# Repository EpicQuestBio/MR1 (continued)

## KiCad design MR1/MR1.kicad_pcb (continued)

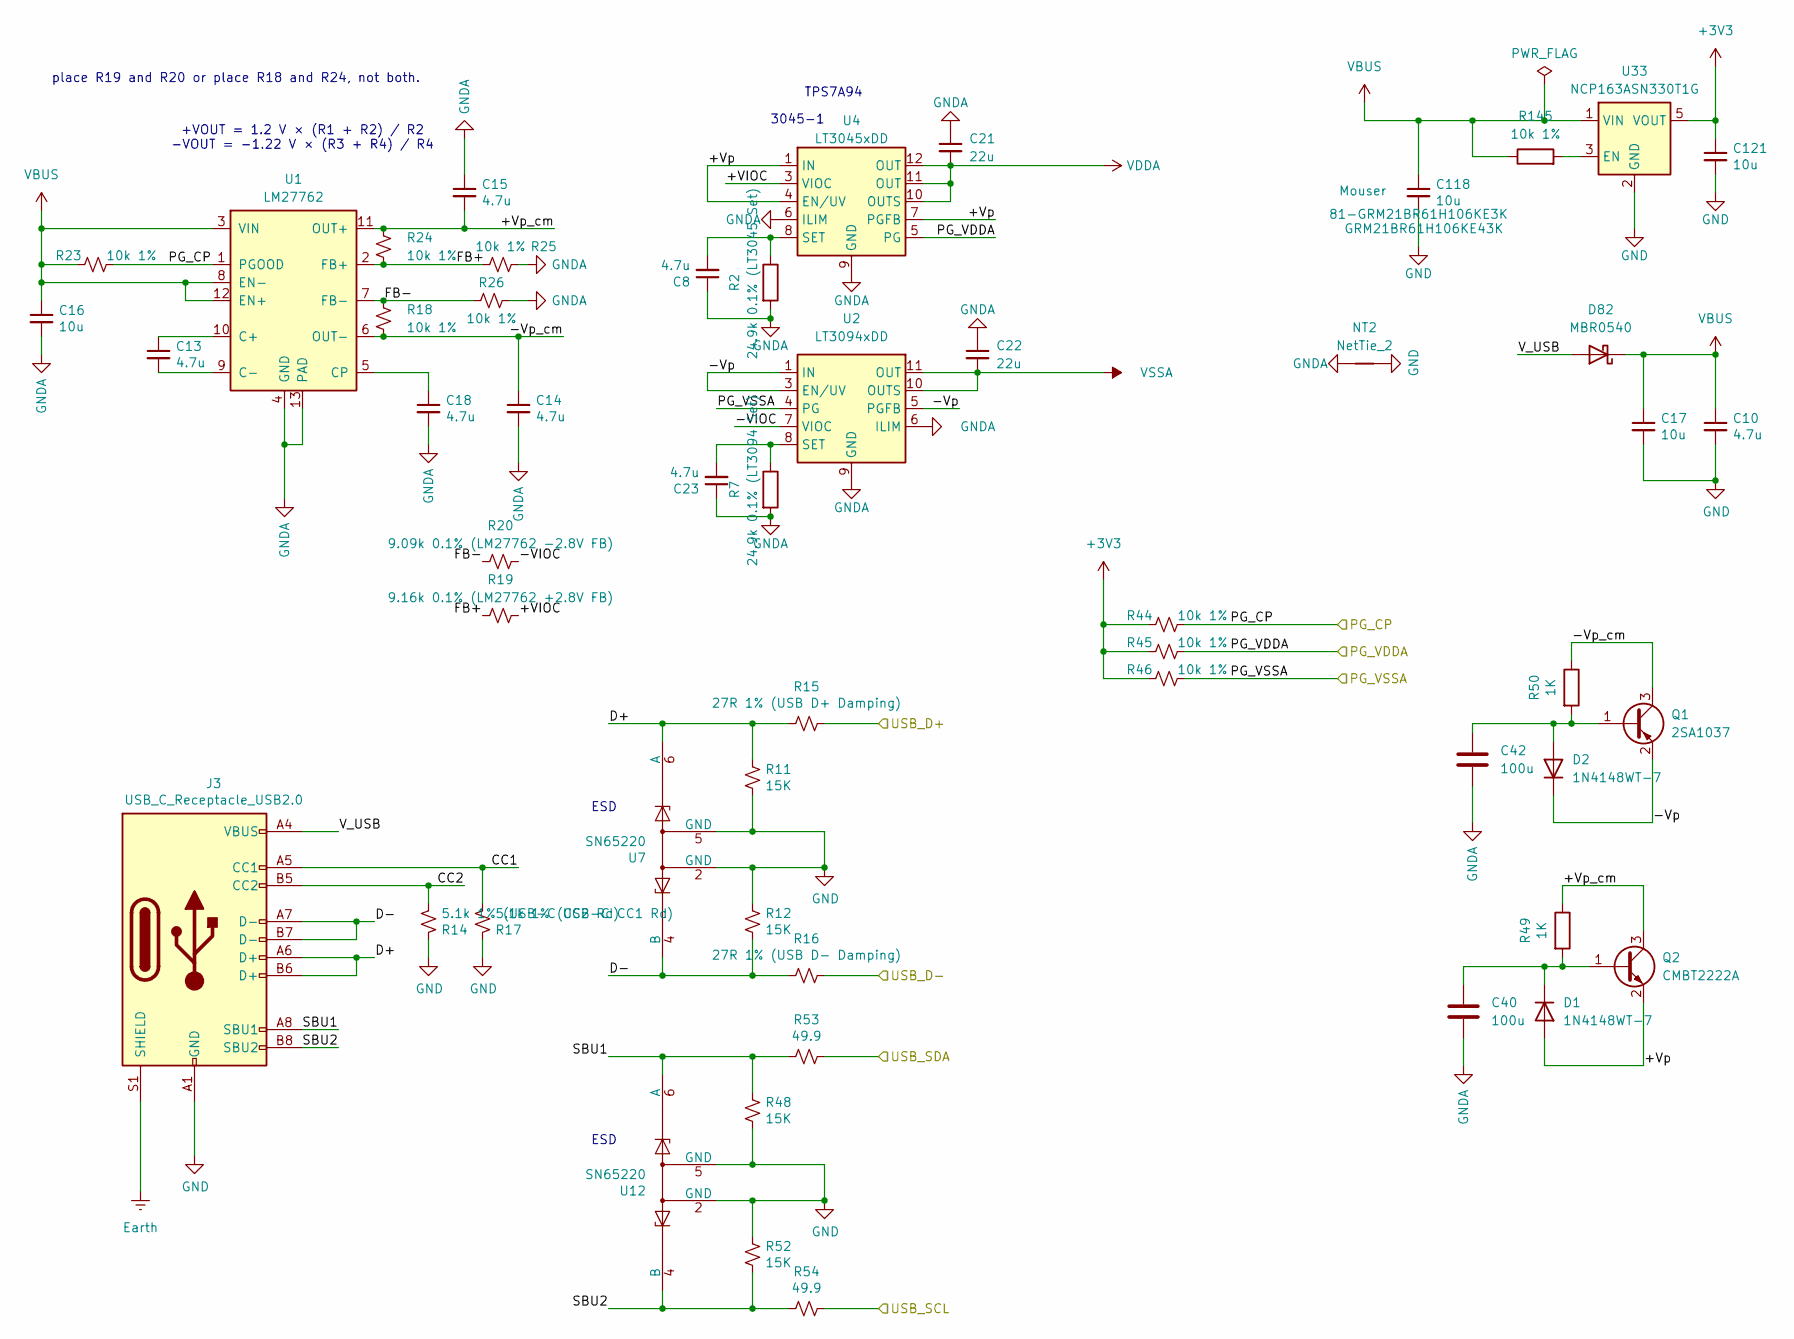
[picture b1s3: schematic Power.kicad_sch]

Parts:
C8, C10, C13, C14, C15, C18, C23: 4.7u; C_0402_1005Metric; Manufacturer_Part_Number JMK107C6475KA-T; LCSC C23733
C16, C17: 10u; C_0402_1005Metric; Manufacturer_Part_Number LMK212ABJ106MG-T; LCSC C15525
C21, C22: 22u; C_0402_1005Metric; MPN GRM21BR61H106KE43K; LCSC C2762589
C40, C42: 100u; C_1206_3216Metric; LCSC C15008
C118, C121: 10u; C_0402_1005Metric; MPN GRM21BR61H106KE43K; LCSC C15525
D1, D2: 1N4148WT-7; D_SOD-523; LCSC C727112
D82: MBR0540; D_SOD-123; MPN MBR0540L-TP; LCSC C5204747
J3: USB_C_Receptacle_USB2.0; USB_C_Receptacle_HRO_TYPE-C-31-M-12; Manufacturer_Part_Number USB4105-GF-A; LCSC C165948
NT2: NetTie_2; NetTie-2_SMD_Pad0.5mm
Q1: 2SA1037; SOT-23; LCSC C2143
Q2: CMBT2222A; SOT-23; LCSC C2152
R2: 24.9k 0.1% (LT3045 Set); R_0402_1005Metric; LCSC C25874
R7: 24.9k 0.1% (LT3094 Set); R_0402_1005Metric; LCSC C25874
R11, R12, R48, R52: 15K; R_0402_1005Metric; Manufacturer_Part_Number RC0603FR-1315KL; LCSC C25756
R14: 5.1k 1% (USB-C CC2 Rd); R_0402_1005Metric; Manufacturer_Part_Number CR0603-FX-5101ELF; LCSC C25905
R15: 27R 1% (USB D+ Damping); R_0402_1005Metric; Manufacturer_Part_Number RK73B1JTTDD270J; LCSC C25078
R16: 27R 1% (USB D- Damping); R_0402_1005Metric; Manufacturer_Part_Number RK73B1JTTDD270J; LCSC C25078
R17: 5.1k 1% (USB-C CC1 Rd); R_0402_1005Metric; Manufacturer_Part_Number CR0603-FX-5101ELF; LCSC C25905
R18, R23, R24, R25, R26, R44, R45, R46, R145: 10k 1%; R_0402_1005Metric; MPN RK73H1ETTPB1002F; LCSC C60490
R19: 9.16k 0.1% (LM27762 +2.8V FB); R_0402_1005Metric; MPN RK73H1ETTPB1002F; LCSC C11549
R20: 9.09k 0.1% (LM27762 -2.8V FB); R_0402_1005Metric; MPN RK73H1ETTPB1002F; LCSC C25879
R49, R50: 1K; R_0402_1005Metric; LCSC C11702
R53, R54: 49.9; R_0402_1005Metric; Manufacturer_Part_Number RK73B1JTTDD270J; LCSC C87044
U1: LM27762; WSON-12-1EP_3x2mm_P0.5mm_EP1x2.65_ThermalVias; MPN LM27762DSSR; LCSC C473398
U2: LT3094xDD; DFN-12-1EP_3x3mm_P0.45mm_EP1.65x2.38mm_ThermalVias; LCSC C670493
U4: LT3045xDD; DFN-12-1EP_3x3mm_P0.5mm_EP1.6x2.5mm; MPN LT3045EDD-1#TRPBF; LCSC C514420
U7, U12: SN65220; SOT-23-6; Manufacturer_Part_Number SN65220DBVT; LCSC C21787
U33: NCP163ASN330T1G; SOT-23-5; MPN NCP163ASN330T1G; LCSC C136082

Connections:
+3V3: C121.1, R44.1, R45.1, R46.1, U33.5 (VOUT); also elsewhere on the board
/Microcontroller/GPIO19: R16.2; also elsewhere on the board
/Microcontroller/GPIO20: R15.2; also elsewhere on the board
/Microcontroller/GPIO21: R53.2; also elsewhere on the board
/Microcontroller/GPIO26: R54.2; also elsewhere on the board
/Power/+VIOC: R19.1, U4.3 (VIOC)
/Power/+Vp: D1.2 (A), Q2.2 (E), U4.1 (IN), U4.2 (IN), U4.4 (EN/UV), U4.7 (PGFB)
/Power/+Vp_cm: C15.2, Q2.3 (C), R24.2, R49.1, U1.11 (OUT+)
/Power/-VIOC: R20.1, U2.7 (VIOC)
/Power/-Vp: D2.1 (K), Q1.2 (E), U2.1 (IN), U2.2 (IN), U2.3 (EN/UV), U2.5 (PGFB), U2.13 (IN)
/Power/-Vp_cm: C14.1, Q1.3 (C), R18.1, R50.1, U1.6 (OUT-)
/Power/CC1: J3.A5 (CC1), R17.2
/Power/CC2: J3.B5 (CC2), R14.2
/Power/D+: J3.A6 (D+), J3.B6 (D+), R11.1, R15.1, U7.1, U7.6 (A)
/Power/D-: J3.A7 (D-), J3.B7 (D-), R12.2, R16.1, U7.3, U7.4 (B)
/Power/FB+: R19.2, R24.1, R25.2, U1.2 (FB+)
/Power/FB-: R18.2, R20.2, R26.1, U1.7 (FB-)
/Power/PG_CP: R23.2, R44.2, U1.1 (PGOOD); also elsewhere on the board
/Power/PG_VDDA: R45.2, U4.5 (PG); also elsewhere on the board
/Power/PG_VSSA: R46.2, U2.4 (PG); also elsewhere on the board
/Power/SBU1: J3.A8 (SBU1), R48.1, R53.1, U12.1, U12.6 (A)
/Power/SBU2: J3.B8 (SBU2), R52.2, R54.1, U12.3, U12.4 (B)
/Power/V_USB: D82.2 (A), J3.A4 (VBUS), J3.A9 (VBUS), J3.B4 (VBUS), J3.B9 (VBUS)
Earth: J3.S1 (SHIELD); also elsewhere on the board
GND: C10.2, C17.2, C118.2, C121.2, J3.A1 (GND), J3.A12 (GND), J3.B1 (GND), J3.B12 (GND), NT2.2, R11.2, R12.1, R14.1, R17.1, R48.2, R52.1, U7.2 (GND), U7.5 (GND), U12.2 (GND), U12.5 (GND), U33.2 (GND); also elsewhere on the board
GNDA: C8.1, C14.2, C15.1, C16.2, C18.2, C21.1, C22.1, C23.1, C40.2, C42.1, NT2.1, R2.2, R7.2, R25.1, R26.2, U1.4 (GND), U1.13 (PAD), U2.6 (ILIM), U2.9 (GND), U4.6 (ILIM), U4.9 (GND), U4.13 (GND); also elsewhere on the board
unnamed: C40.1, D1.1 (K), Q2.1 (B), R49.2
unnamed: C42.2, D2.2 (A), Q1.1 (B), R50.2
unnamed: C13.1, U1.10 (C+)
unnamed: C13.2, U1.9 (C-)
unnamed: C18.1, U1.5 (CP)
unnamed: C23.2, R7.1, U2.8 (SET)
unnamed: C8.2, R2.1, U4.8 (SET)
unnamed: R145.2, U33.3 (EN)
VBUS: C10.1, C16.1, C17.1, C118.1, D82.1 (K), R23.1, R145.1, U1.3 (VIN), U1.8 (EN-), U1.12 (EN+), U33.1 (VIN)
VDDA: C21.2, U4.10 (OUTS), U4.11 (OUT), U4.12 (OUT); also elsewhere on the board
VSSA: C22.2, U2.10 (OUTS), U2.11 (OUT), U2.12 (OUT); also elsewhere on the board

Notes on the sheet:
ESD
+VOUT = 1.2 V × (R1 + R2) / R2 -VOUT = -1.22 V × (R3 + R4) / R4
3045-1
TPS7A94
place R19 and R20 or place R18 and R24, not both.

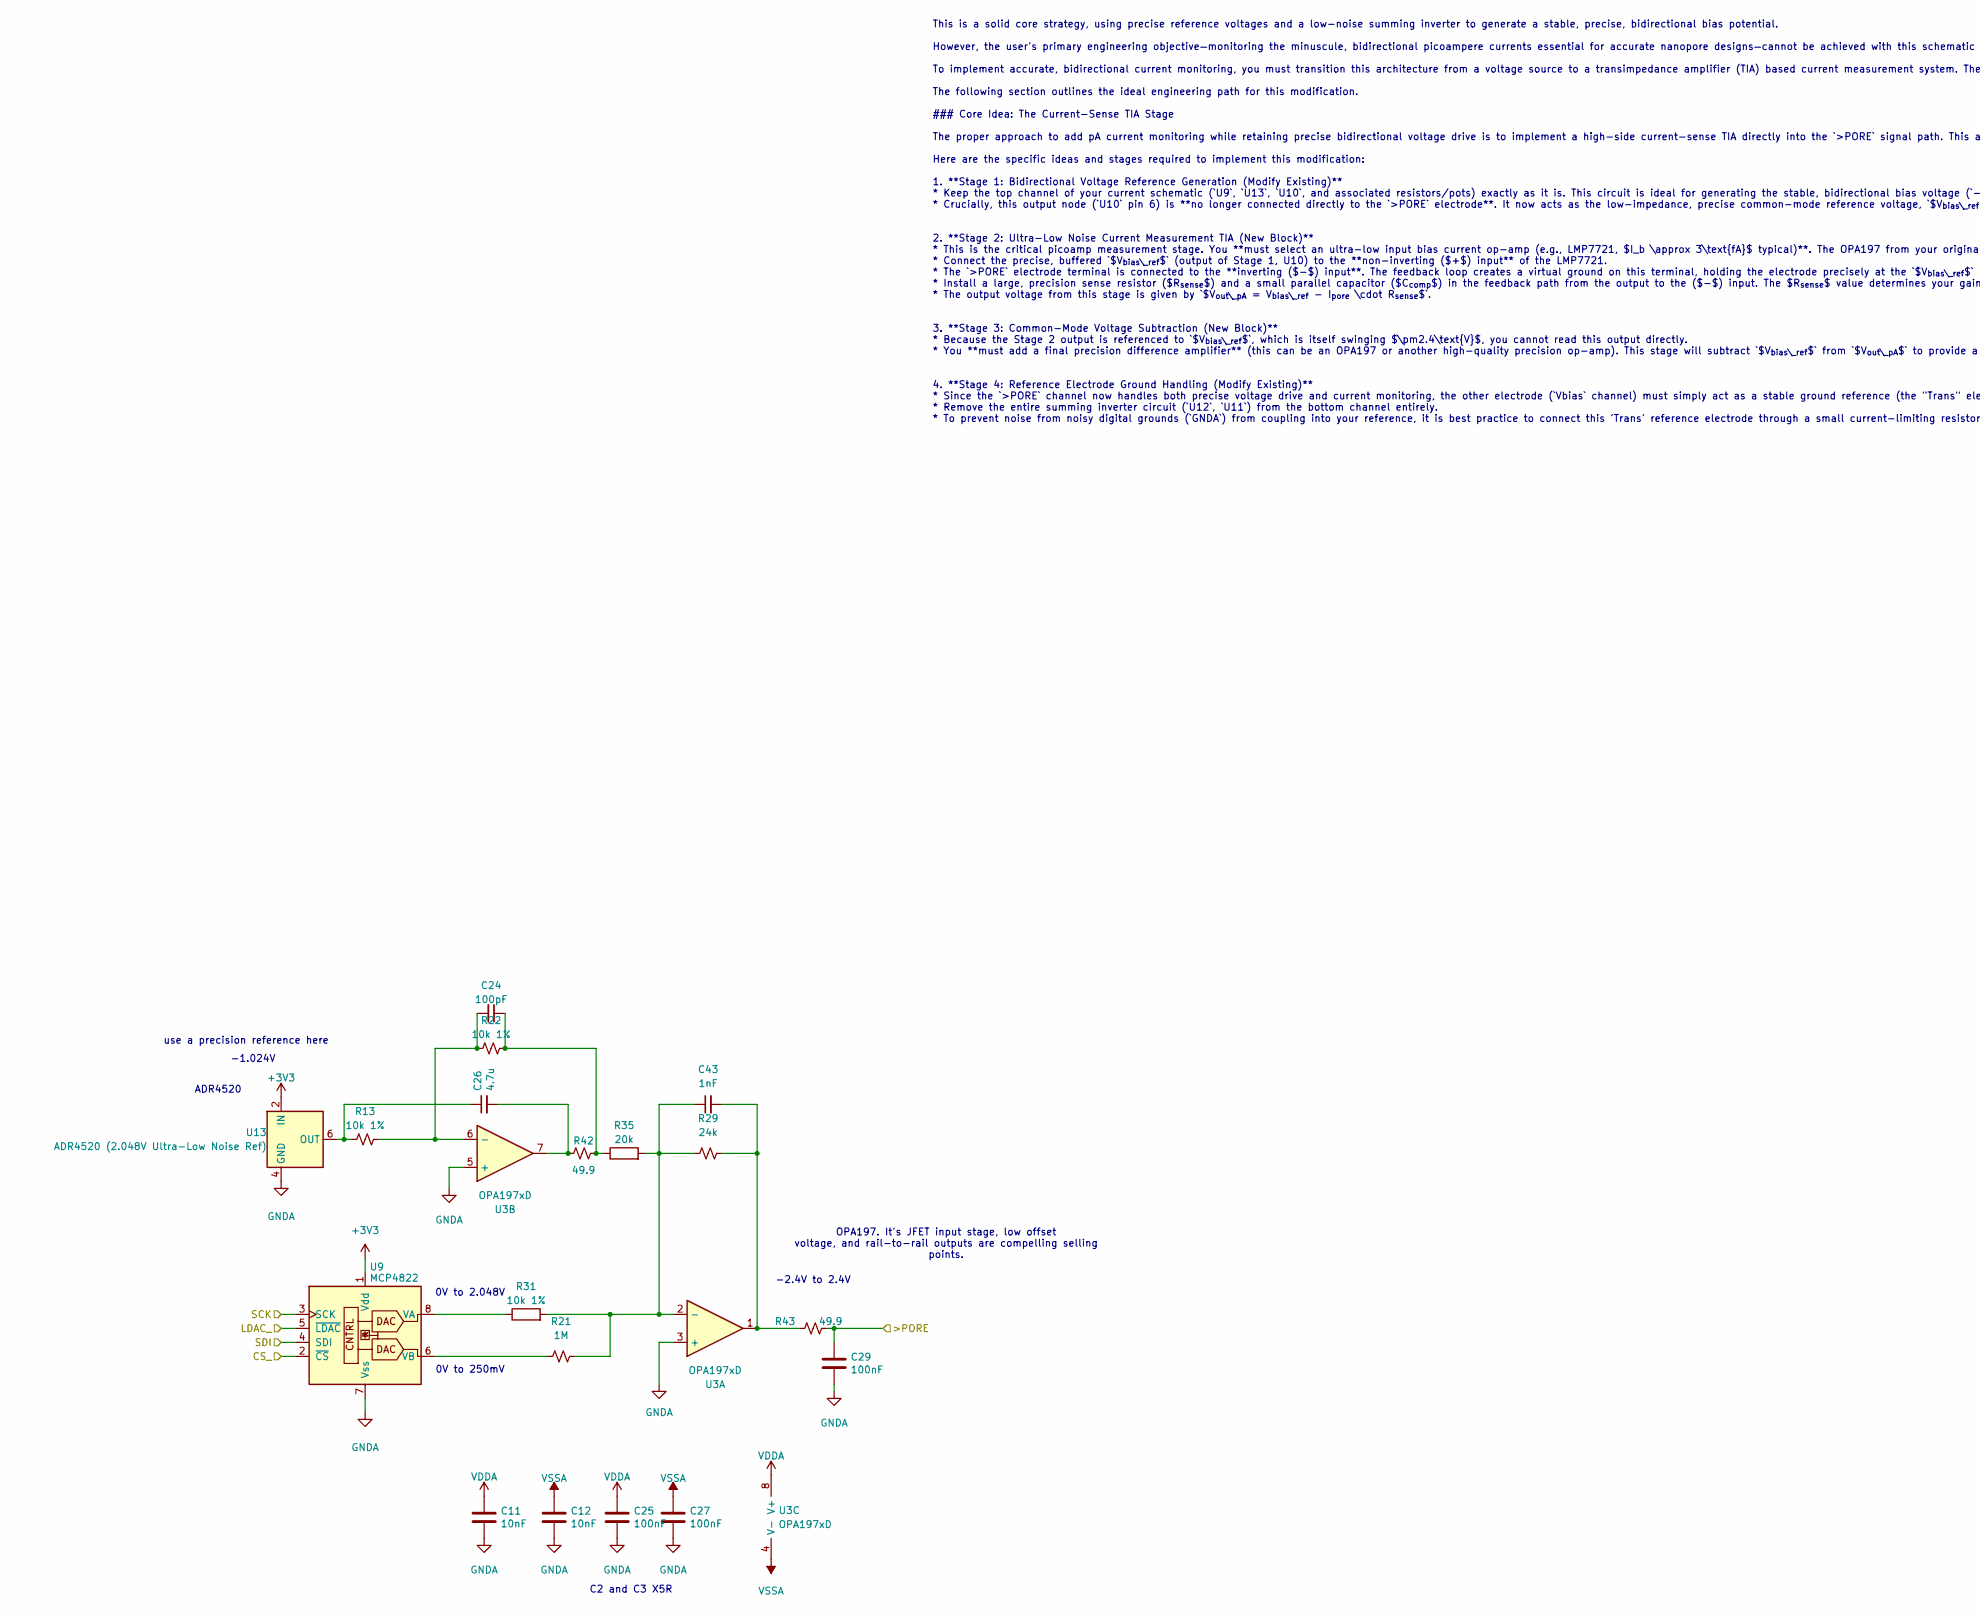
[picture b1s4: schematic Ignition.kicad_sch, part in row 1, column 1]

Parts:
C11, C12: 10nF; C_0402_1005Metric; LCSC C15195
C24: 100pF; C_0402_1005Metric; Manufacturer_Part_Number 0402CG101J500NT; LCSC C1546
C25, C27, C29: 100nF; C_0402_1005Metric; LCSC C1525
C26: 4.7u; C_0402_1005Metric; Manufacturer_Part_Number JMK107C6475KA-T; LCSC C23733
C43: 1nF; C_0402_1005Metric; LCSC C1523
R13, R22: 10k 1%; R_0402_1005Metric; MPN RK73H1ETTPB1002F; LCSC C60490
R21: 1M; R_0402_1005Metric; MPN 0402WGF1004TCE; LCSC C26083
R29: 24k; R_0402_1005Metric; MPN RK73H1ETTPB1002F; LCSC C25769
R31: 10k 1%; R_0402_1005Metric; LCSC C60490
R35: 20k; R_0402_1005Metric; LCSC C25765
R42, R43: 49.9; R_0402_1005Metric; MPN RC0402JR-0727RL; LCSC C87044
U3: OPA197xD; VSSOP-8_3x3mm_P0.65mm; MPN OPA197IDGKT; LCSC C133554
U9: MCP4822; SOIC-8-1EP_3.9x4.9mm_P1.27mm_EP2.29x3mm; MPN MCP4822T-E/SN; LCSC C16040
U13: ADR4520 (2.048V Ultra-Low Noise Ref); SOIC-8_3.9x4.9mm_P1.27mm; MPN ADR4520ARZ-R7; LCSC C659578

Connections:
+3V3: U9.1 (Vdd), U13.2 (IN); also elsewhere on the board
/Ignition/>PORE: C29.1, R43.2; also elsewhere on the board
/Ignition/CS_: U9.2 (~CS); also elsewhere on the board
/Ignition/LDAC_: U9.5 (~LDAC); also elsewhere on the board
/Ignition/SCK: U9.3 (SCK); also elsewhere on the board
/Ignition/SDI: U9.4 (SDI); also elsewhere on the board
GNDA: C11.2, C12.2, C25.2, C27.2, C29.2, U3.3 (+), U3.5 (+), U9.7 (Vss), U13.4 (GND); also elsewhere on the board
unnamed: C24.1, R22.1, R35.1, R42.2
unnamed: C26.2, R42.1, U3.7
unnamed: C43.2, R29.1, R43.1, U3.1
unnamed: C43.1, R21.1, R29.2, R31.2, R35.2, U3.2 (-)
unnamed: C24.2, R13.1, R22.2, U3.6 (-)
unnamed: R31.1, U9.8 (VA)
unnamed: R21.2, U9.6 (VB)
unnamed: C26.1, R13.2, U13.6 (OUT)
VDDA: C11.1, C25.1, U3.8 (V+); also elsewhere on the board
VSSA: C12.1, C27.1, U3.4 (V-); also elsewhere on the board

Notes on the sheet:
use a precision reference here
This is a solid core strategy, using precise reference voltages and a low-noise summing inverter to generate a stable, precise, bidirectional bias potential. However, the user's primary engineering objective—monitoring the minuscule, bidirectional picoampere currents essential for accurate nanopore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
0V to 250mV
C2 and C3 X5R
-2.4V to 2.4V
OPA197. It's JFET input stage, low offset voltage, and rail-to-rail outputs are compelling selling points.
ADR4520
0V to 2.048V
-1.024V

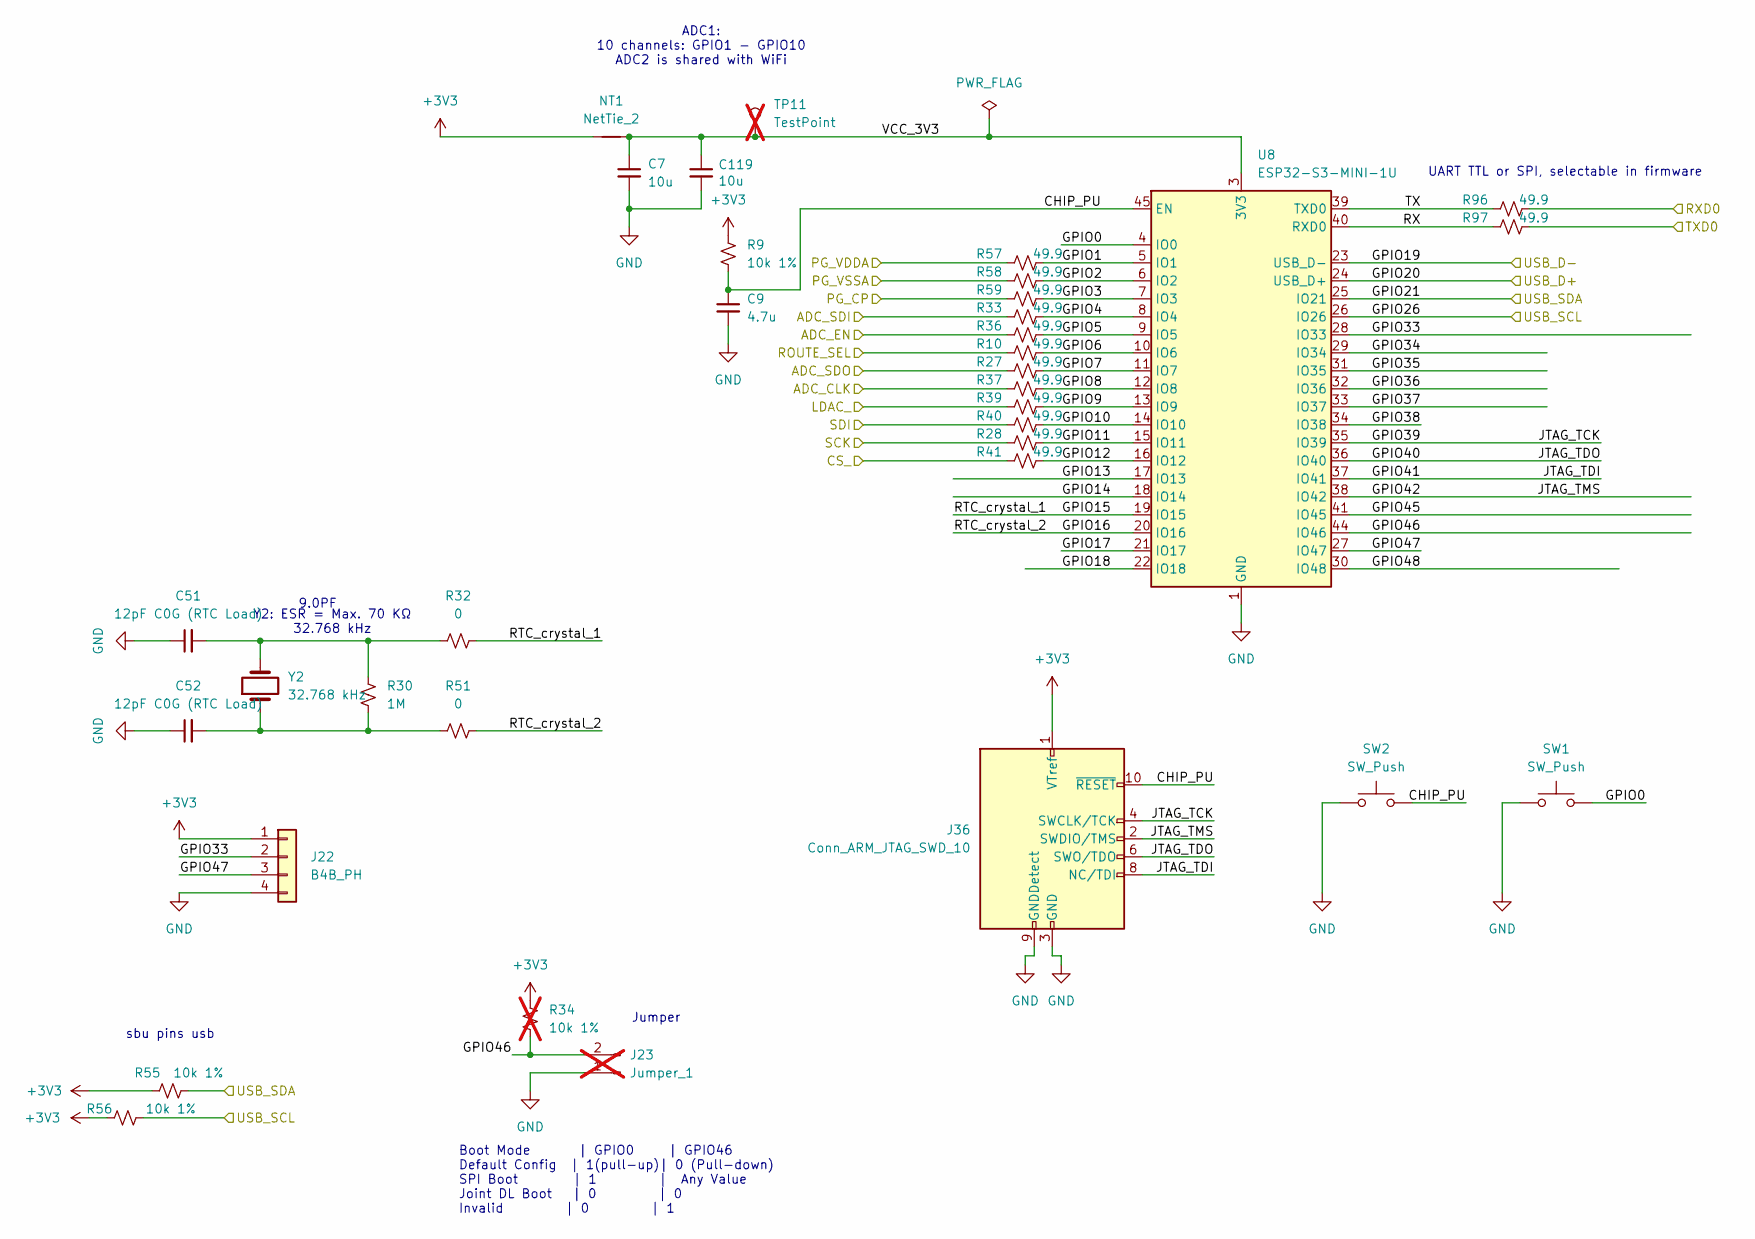
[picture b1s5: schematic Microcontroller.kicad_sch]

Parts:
C7, C119: 10u; C_0402_1005Metric; MPN GRM21BR61H106KE43K; LCSC C15525
C9: 4.7u; C_0402_1005Metric; MPN LMK107BJ475KA-T; LCSC C23733
C51, C52: 12pF C0G (RTC Load); C_0402_1005Metric; MPN 0402YA120JAT2A; LCSC C1550
J22: B4B_PH; JST_PH_B4B-PH-K_1x04_P2.00mm_Vertical; MPN B4B-PH-K-S; LCSC C131334
J23: Jumper_1; PinHeader_1x02_P2.54mm_Vertical; LCSC C492401; not fitted
J36: Conn_ARM_JTAG_SWD_10; PinHeader_2x05_P1.27mm_Vertical_SMD; MPN FTSH-105-01-F-DV-007-P-TR; LCSC C42372555
NT1: NetTie_2; NetTie-2_SMD_Pad0.5mm
R9, R55, R56: 10k 1%; R_0402_1005Metric; MPN RK73H1ETTPB1002F; LCSC C60490
R10, R27, R28, R33, R36, R37, R39, R40, R41, R57, R58, R59, R96, R97: 49.9; R_0402_1005Metric; MPN RC0402JR-0727RL; LCSC C87044
R30: 1M; R_0402_1005Metric; MPN CRCW04021M00DHEDP; LCSC C26083
R32, R51: 0; R_0402_1005Metric; MPN CRCW04020000Z0EDC; LCSC C17168
R34: 10k 1%; R_0402_1005Metric; MPN RK73H1ETTPB1002F; LCSC C60490; not fitted
SW1, SW2: SW_Push; SW_Push_1P1T_XKB_TS-1187A; MPN TS-1187A-B-A-B; LCSC C318884
TP11: TestPoint; TestPoint_Pad_D1.0mm; not fitted
U8: ESP32-S3-MINI-1U; ESP32-S2-MINI-1U; MPN ESP32-S3-MINI-1U-N8; LCSC C2980299
Y2: 32.768 kHz; Crystal_SMD_3215-2Pin_3.2x1.5mm; MPN FC3215AN 32.768K-90NN60KC5; LCSC C620155

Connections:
+3V3: J22.1, J36.1 (VTref), NT1.1, R9.1, R34.1, R55.1, R56.2; also elsewhere on the board
/Ignition/CS_: R41.1; also elsewhere on the board
/Ignition/LDAC_: R39.1; also elsewhere on the board
/Ignition/SCK: R28.1; also elsewhere on the board
/Ignition/SDI: R40.1; also elsewhere on the board
/Insturmentation/ADC_CLK: R37.1; also elsewhere on the board
/Insturmentation/ADC_EN: R36.1; also elsewhere on the board
/Insturmentation/ADC_SDI: R33.1; also elsewhere on the board
/Insturmentation/ADC_SDO: R27.1; also elsewhere on the board
/Insturmentation/ROUTE_SEL: R10.1; also elsewhere on the board
/Microcontroller/CHIP_PU: C9.1, J36.10 (~RESET), R9.2, SW2.2, U8.45 (EN)
/Microcontroller/GPIO0: SW1.2, U8.4 (IO0)
/Microcontroller/GPIO1: R57.2, U8.5 (IO1)
/Microcontroller/GPIO2: R58.2, U8.6 (IO2)
/Microcontroller/GPIO3: R59.2, U8.7 (IO3)
/Microcontroller/GPIO4: R33.2, U8.8 (IO4)
/Microcontroller/GPIO5: R36.2, U8.9 (IO5)
/Microcontroller/GPIO6: R10.2, U8.10 (IO6)
/Microcontroller/GPIO7: R27.2, U8.11 (IO7)
/Microcontroller/GPIO8: R37.2, U8.12 (IO8)
/Microcontroller/GPIO9: R39.2, U8.13 (IO9)
/Microcontroller/GPIO10: R40.2, U8.14 (IO10)
/Microcontroller/GPIO11: R28.2, U8.15 (IO11)
/Microcontroller/GPIO12: R41.2, U8.16 (IO12)
/Microcontroller/GPIO13: U8.17 (IO13)
/Microcontroller/GPIO14: U8.18 (IO14)
/Microcontroller/GPIO15: R32.2, U8.19 (IO15)
/Microcontroller/GPIO16: R51.1, U8.20 (IO16)
/Microcontroller/GPIO17: U8.21 (IO17)
/Microcontroller/GPIO18: U8.22 (IO18)
/Microcontroller/GPIO19: U8.23 (USB_D-); also elsewhere on the board
/Microcontroller/GPIO20: U8.24 (USB_D+); also elsewhere on the board
/Microcontroller/GPIO21: R55.2, U8.25 (IO21); also elsewhere on the board
/Microcontroller/GPIO26: R56.1, U8.26 (IO26); also elsewhere on the board
/Microcontroller/GPIO33: J22.2, U8.28 (IO33)
/Microcontroller/GPIO34: U8.29 (IO34)
/Microcontroller/GPIO35: U8.31 (IO35)
/Microcontroller/GPIO36: U8.32 (IO36)
/Microcontroller/GPIO37: U8.33 (IO37)
/Microcontroller/GPIO38: U8.34 (IO38)
/Microcontroller/GPIO39: J36.4 (SWCLK/TCK), U8.35 (IO39)
/Microcontroller/GPIO40: J36.6 (SWO/TDO), U8.36 (IO40)
/Microcontroller/GPIO41: J36.8 (NC/TDI), U8.37 (IO41)
/Microcontroller/GPIO42: J36.2 (SWDIO/TMS), U8.38 (IO42)
/Microcontroller/GPIO45: U8.41 (IO45)
/Microcontroller/GPIO46: J23.2, R34.2, U8.44 (IO46)
/Microcontroller/GPIO47: J22.3, U8.27 (IO47)
/Microcontroller/GPIO48: U8.30 (IO48)
/Microcontroller/RX: R97.1, U8.40 (RXD0)
/Microcontroller/RXD0: R96.2
/Microcontroller/TX: R96.1, U8.39 (TXD0)
/Microcontroller/TXD0: R97.2
/Microcontroller/VCC_3V3: C7.1, C119.1, NT1.2, TP11.1 (1_1), U8.3 (3V3)
/Power/PG_CP: R59.1; also elsewhere on the board
/Power/PG_VDDA: R57.1; also elsewhere on the board
/Power/PG_VSSA: R58.1; also elsewhere on the board
GND: C7.2, C9.2, C51.1, C52.1, C119.2, J22.4, J23.1, J36.3 (GND), J36.5 (GND), J36.9 (GNDDetect), SW1.1, SW2.1, U8.1 (GND), U8.2 (GND), U8.42 (GND), U8.43 (GND), U8.46 (GND), U8.47 (GND), U8.48 (GND), U8.49 (GND), U8.50 (GND), U8.51 (GND), U8.52 (GND), U8.53 (GND), U8.54 (GND), U8.55 (GND), U8.56 (GND), U8.57 (GND), U8.58 (GND), U8.59 (GND), U8.60 (GND), U8.61 (GND), U8.62 (GND), U8.63 (GND), U8.64 (GND), U8.65 (GND); also elsewhere on the board
unnamed: C51.2, R30.1, R32.1, Y2.2
unnamed: C52.2, R30.2, R51.2, Y2.1

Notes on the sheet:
Jumper
9.0PF
UART TTL or SPI, selectable in firmware
Boot Mode | GPIO0 | GPIO46 Default Config | 1(pull-up)| 0 (Pull-down) SPI Boot | 1 | Any Value Joint DL Boot | 0 | 0 Invalid | 0 | 1
Y2: ESR = Max. 70 KΩ 32.768 kHz
sbu pins usb
ADC1: 10 channels: GPIO1 - GPIO10 ADC2 is shared with WiFi

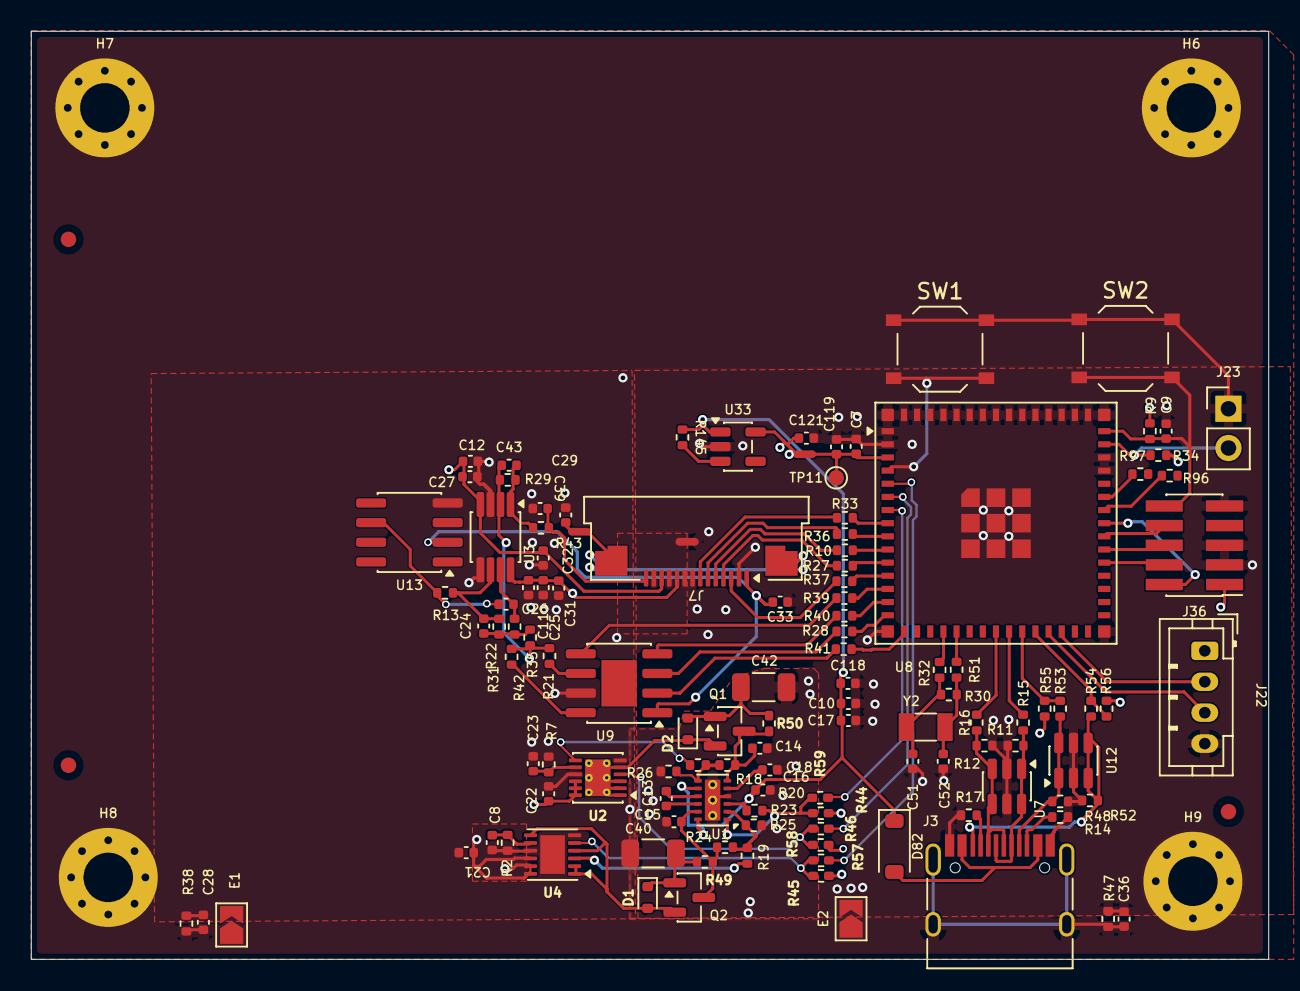
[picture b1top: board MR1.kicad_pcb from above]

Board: 4 copper layers, 80.0 x 60.0 mm, 126 parts (0 on the bottom side), 85 nets.

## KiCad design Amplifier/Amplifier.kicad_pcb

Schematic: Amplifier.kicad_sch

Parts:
C7, C8: 10nF; C_0402_1005Metric; LCSC C15195
C10, C12, C39: 100nF; C_0402_1005Metric; LCSC C1525
FID1, FID2, FID3: Fiducial_1mm_Mask2mm
J7: Conn_01x14_MountingPin; XUNPU_FPC-05F-14PH15_1x14_P0.5mm_Horizontal; LCSC C2856818
NT4: NetTie_3; NetTie-3_SMD_ShieldPad_2.5x3.6mm
NT7: NetTie_2; NetTie-2_SMD_Pad0.5mm
P1, P3, P4, P7, P8, P9, P10, P11, P12: PogoPin_MillMax_SMT_1Pin; LCSC C5221285
P2, P5: PogoPin_MillMax_SMT_1Pin_Guarded; PogoPin_SMT_Circle_Guard_Notched; LCSC C5221285
R28, R29, R30, R31, R33: 49.9; R_0402_1005Metric; MPN RC0402JR-0727RL; LCSC C87044
SYM1: SYM_Arrow45_Large; Fluid_Overlay_SILKSCREEN_ONLY

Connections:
+3V3: J7.1; also elsewhere on the board
/>PORE_AMP: J7.14, P9.1 (PIN_1); also elsewhere on the board
/CE_GNDA: P7.1 (PIN_1); also elsewhere on the board
/GDAC_CLK: R31.1; also elsewhere on the board
/GDAC_EN: R29.1; also elsewhere on the board
/GDAC_SDI: R30.1; also elsewhere on the board
/GDAC_SDO: R33.1; also elsewhere on the board
/GNDA_SHLD: NT4.3, P1.1 (PIN_1)
/GNDA_WEEP: P12.1 (PIN_1); also elsewhere on the board
/GUARD: P4.1 (PIN_1), P5.2 (GUARD); also elsewhere on the board
/GUARD_WIDE: P2.2 (GUARD), P3.1 (PIN_1); also elsewhere on the board
/RE_TRANS: P8.1 (PIN_1); also elsewhere on the board
/ROUTE_SEL: R28.1; also elsewhere on the board
/SHIELD: NT4.1, NT7.2
/SHIELD_AMP: J7.MP (MountPin), NT4.2
/WEEP_SENSE: P11.1 (PIN_1); also elsewhere on the board
/WS_CIS: P5.1 (SIG); also elsewhere on the board
/WS_CIS_WIDE: P2.1 (SIG); also elsewhere on the board
GND: J7.2, J7.8
GNDA: C7.2, C8.2, C10.2, C12.2, C39.2, J7.9, J7.11, J7.13, P10.1 (PIN_1); also elsewhere on the board
unnamed: C39.1, NT7.1
unnamed: J7.3, R31.2
unnamed: J7.4, R33.2
unnamed: J7.5, R28.2
unnamed: J7.6, R29.2
unnamed: J7.7, R30.2
VDDA: C7.1, C10.1, J7.10; also elsewhere on the board
VSSA: C8.1, C12.1, J7.12; also elsewhere on the board

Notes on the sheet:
SM10B-SRSS-TB
3. Selecting the Precision ADC To capture <1µV signals, you need a 24-bit or 32-bit Delta-Sigma ADC. The standard 12-bit or 16-bit SAR ADCs used in microcontrollers will not see the signal floor you have created. Top Recommendations: TI ADS1261 (24-bit / 32-bit mode): Why: It has a built-in PGA (Pr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
Ceramic capacitors are piezoelectric – mechanical vibrations and noises will create charge across the capacitor. Be careful when using ceramic caps in the input, integration, feedback or biasing networks.
consider cat 7 flat ribbon cable, 8 pairs, shielded
Stability in ultra-low noise regulators is dictated by the **Output Capacitance ()** and the **Noise Reduction Capacitance ()**. If these ratios are wrong, the LDO will oscillate, turning your "clean" power supply into a radio transmitter. ### 1. The LDO Component Values (The Critical Stage) These 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
https://www.vpi.us/bulk-cable-sf/super-flat-cat7-736#idTab9
RF-damping capacitor
For high-speed nanopore sensing, the answer is definitive: **Do NOT tie them together.** You should use **Separate Voltage References** (or at least strictly buffered separate paths) for your ADC and your Bias Driver. Here is the engineering reality of why sharing a "Reference Rail" will introduce 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
Old notes
No, the schematic recipe I provided above is **Fixed Gain (10x)**. It uses a standard resistor, so the zoom level is locked. Since you are removing the MAX9939 (which *was* a variable gain amplifier), you likely want to keep that functionality—especially since Nanopores vary wildly in current. A 1 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
we need to play back a waveform
250ft 32AWG CAT7 STP Solid, 0.075" Super Flat Bulk Ethernet Bare Copper Cable - White.
Using an **Optically Isolated Current Source (LED + Photodiode)** is the "Ferrari" of dummy loads for nanopore amplifiers. While the resistor method (like in the EarlGrey PDF) is great for checking baseline noise, the LED/Photodiode method is superior for checking **bandwidth** and **step response*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
pins for holding the board in place while applying adhesive https://www.mcmaster.com/98378A208/
SSH-003T-P0.2-H #32 to #28 (0.032 to 0.081) 0.4 to 0.8 23,000
SHR-10V-S
C2 and C3 X5R

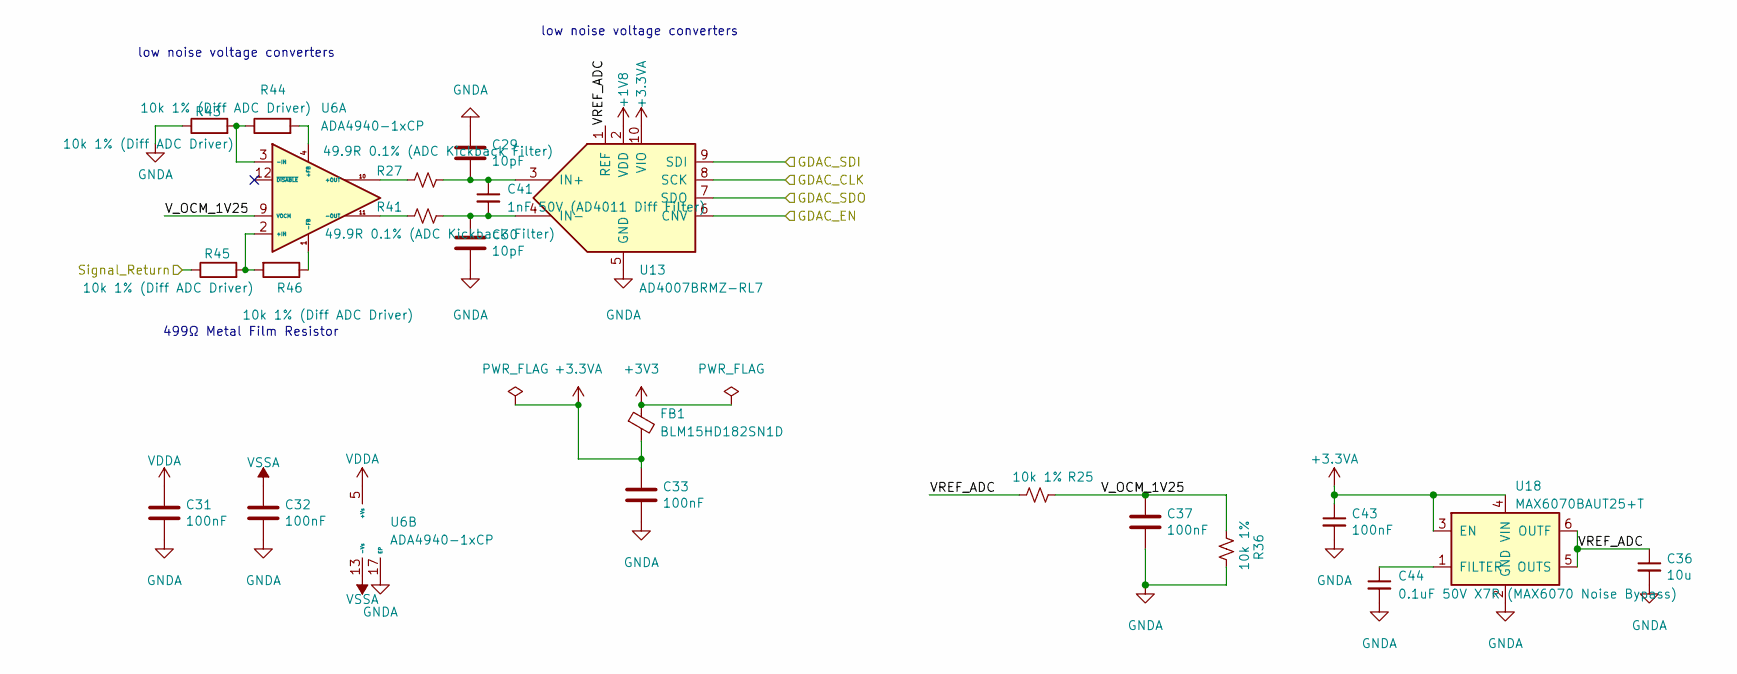
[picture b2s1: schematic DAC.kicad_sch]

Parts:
C29, C30: 10pF; C_0402_1005Metric; LCSC C32949
C31, C32, C33, C37: 100nF; C_0402_1005Metric; LCSC C1525
C36: 10u; C_0402_1005Metric; MPN GRM21BR61H106KE43K; LCSC C15525
C41: 1nF 50V (AD4011 Diff Filter); C_0402_1005Metric; LCSC C1523
C43: 100nF; C_0402_1005Metric; MPN 0402B104K500NT; LCSC C1525
C44: 0.1uF 50V X7R (MAX6070 Noise Bypass); C_0402_1005Metric; MPN 0402B104K500NT; LCSC C1525
FB1: BLM15HD182SN1D; L_0402_1005Metric; LCSC C76888
R25: 10k 1%; R_0402_1005Metric; MPN RK73H1ETTPB1002F; LCSC C60490
R27, R41: 49.9R 0.1% (ADC Kickback Filter); R_0402_1005Metric; MPN 0402WGF499JTCE; LCSC C87044
R36: 10k 1%; R_0402_1005Metric; MPN 0402WGF1002TCE; LCSC C60490
R43, R44, R45, R46: 10k 1% (Diff ADC Driver); R_0402_1005Metric; LCSC C60490
U6: ADA4940-1xCP; LFCSP-16-1EP_3x3mm_P0.5mm_EP1.3x1.3mm_ThermalVias; MPN ADA4940-1ACPZ-RL; LCSC C468516
U13: AD4007BRMZ-RL7; MSOP-10_3x3mm_P0.5mm; MPN AD4007BRMZ-RL7; LCSC C649158
U18: MAX6070BAUT25+T; SOT-23-6; MPN MAX6070BAUT25+T; LCSC C143531

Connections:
+1V8: U13.2 (VDD); also elsewhere on the board
+3.3VA: C33.1, C43.1, FB1.2, U13.10 (VIO), U18.3 (EN), U18.4 (VIN); also elsewhere on the board
+3V3: FB1.1; also elsewhere on the board
/DAC/VREF_ADC: C36.1, R25.2, U13.1 (REF), U18.5 (OUTS), U18.6 (OUTF)
/DAC/V_OCM_1V25: C37.1, R25.1, R36.1, U6.9 (VOCM)
/GDAC_CLK: U13.8 (SCK); also elsewhere on the board
/GDAC_EN: U13.6 (CNV); also elsewhere on the board
/GDAC_SDI: U13.9 (SDI); also elsewhere on the board
/GDAC_SDO: U13.7 (SDO); also elsewhere on the board
/Signal_Return: R45.1; also elsewhere on the board
GNDA: C29.1, C30.2, C31.2, C32.2, C33.2, C36.2, C37.2, C43.2, C44.2, R36.2, R43.1, U6.17 (EP), U13.5 (GND), U18.2 (GND); also elsewhere on the board
unnamed: R44.2, U6.4 (+FB)
unnamed: R45.2, R46.2, U6.2 (+IN)
unnamed: R27.1, U6.10 (+OUT)
unnamed: R46.1, U6.1 (-FB)
unnamed: R43.2, R44.1, U6.3 (-IN)
unnamed: R41.1, U6.11 (-OUT)
unnamed: C29.2, C41.1, R27.2, U13.3 (IN+)
unnamed: C30.1, C41.2, R41.2, U13.4 (IN-)
unnamed: C44.1, U18.1 (FILTER)
VDDA: C31.1, U6.5 (+Vs), U6.6 (+Vs), U6.7 (+Vs), U6.8 (+Vs); also elsewhere on the board
VSSA: C32.1, U6.13 (-Vs), U6.14 (-Vs), U6.15 (-Vs), U6.16 (-Vs); also elsewhere on the board

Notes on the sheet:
low noise voltage converters
499Ω Metal Film Resistor
